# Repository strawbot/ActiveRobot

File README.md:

# Manifesto
In nature everything is connected. Inside, outside and inside to outside separated by membranes, or highly differentiated regions separating realms. The partitioning of realms and connecting of realms is life. Biomimetic forms seek to have this strategy as a backbone or more broadly, a shell. Within this shell is connectedness. A reticulated ecosystem. Through physical and time connections by remembered pasts and events. Life is lived, learned and lauded. Sometimes forgotten to relive anew. There must be sensing, filtering, analyzing, remembering, planning, pruning, and learning.

# Mission Statement
The decision to change the level of actuation in a single muscle is connected to a funnel of remembrance and motivation. A muscle also feels its actuation, usage, condition, pain and preservation. A muscle can be measured, filtered and categorized into reactions and remembered to effect a trend of behaviour. Sense of balance, change in balance, flight plan for balance all form the actuations of muscle seeking to achieve balance motivation.

# Notes
- Each board port of the platform has its own project, differences and abilities
- As abilities are developed, they can be shared and moved to the Robot folder
- Network connectivity is possible via Ethernet, USB, and PPP over serial
- Shared network applications include NTP, Telnet, HTTP
- The HTTP web server provides a way to communicate with the board through a command line and observe robotic elements via a line graph and 3D visual element

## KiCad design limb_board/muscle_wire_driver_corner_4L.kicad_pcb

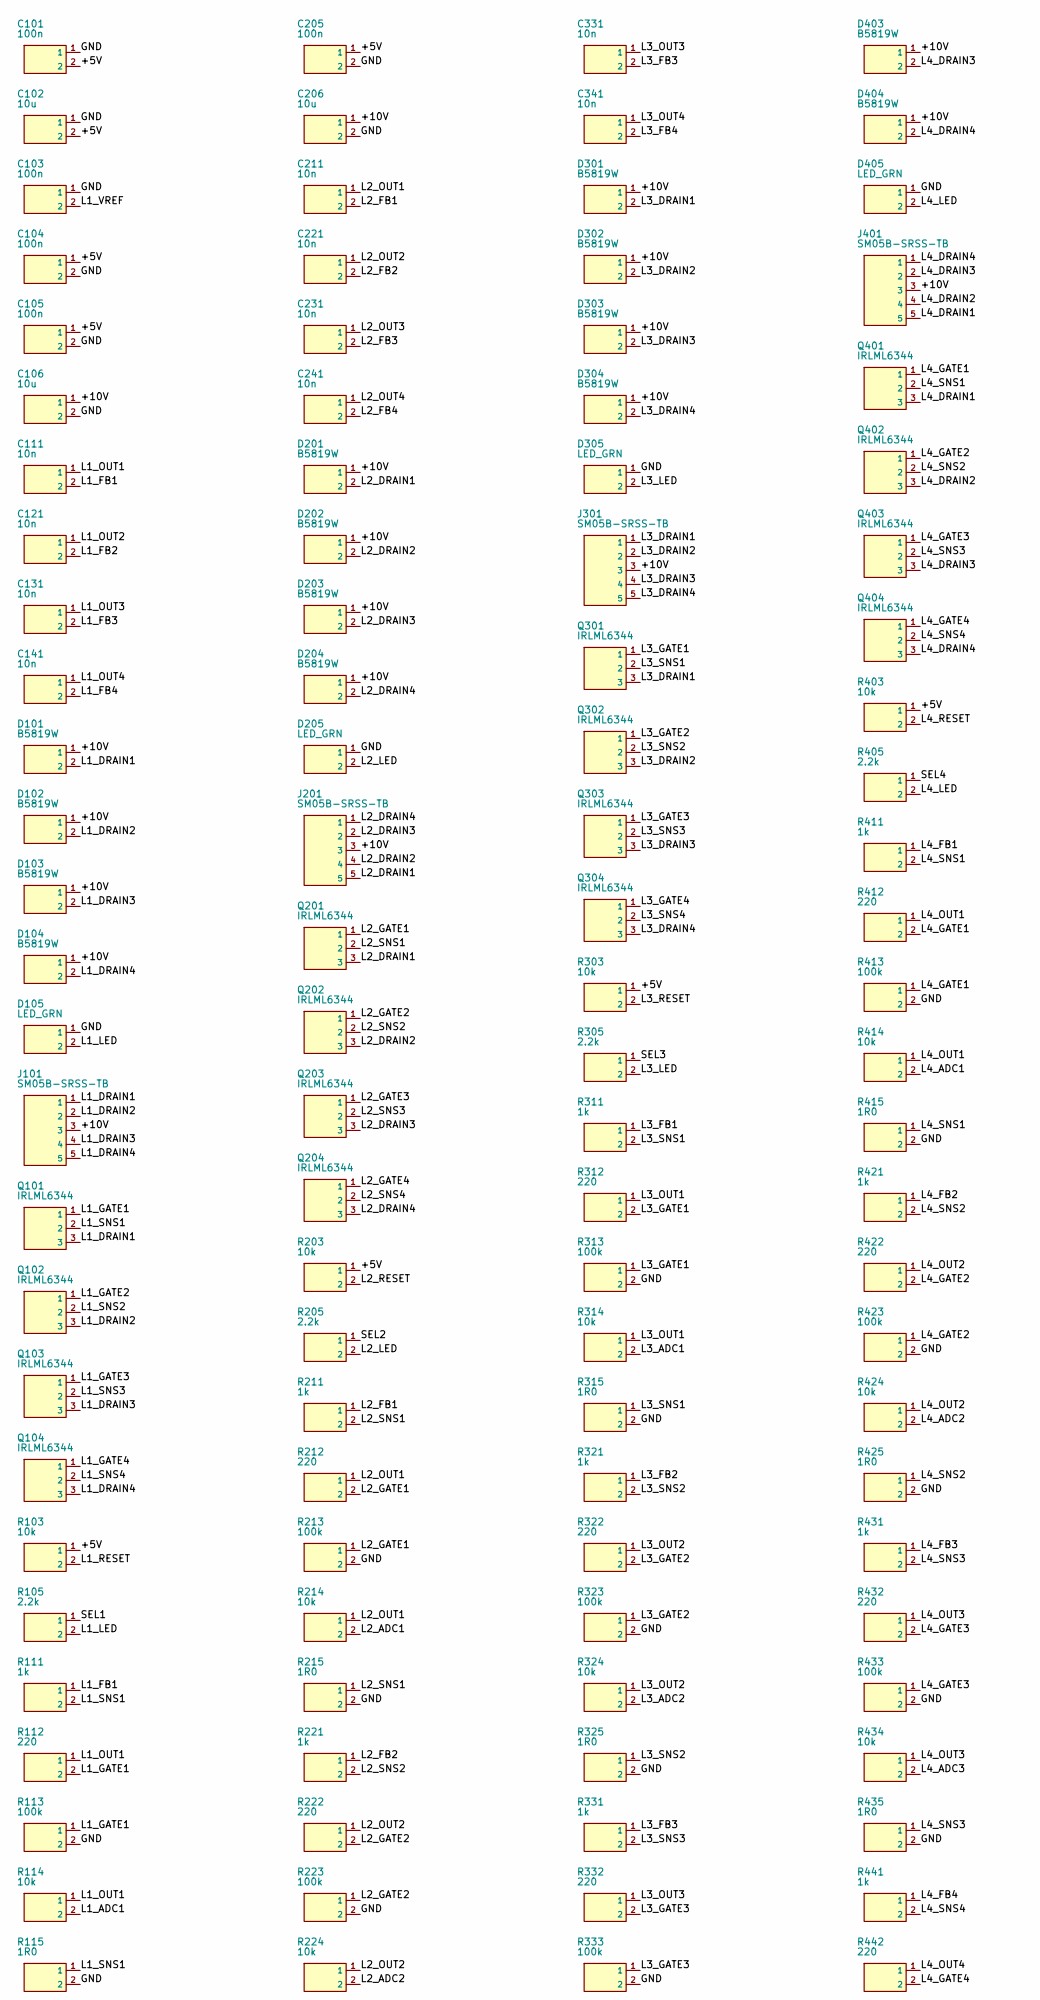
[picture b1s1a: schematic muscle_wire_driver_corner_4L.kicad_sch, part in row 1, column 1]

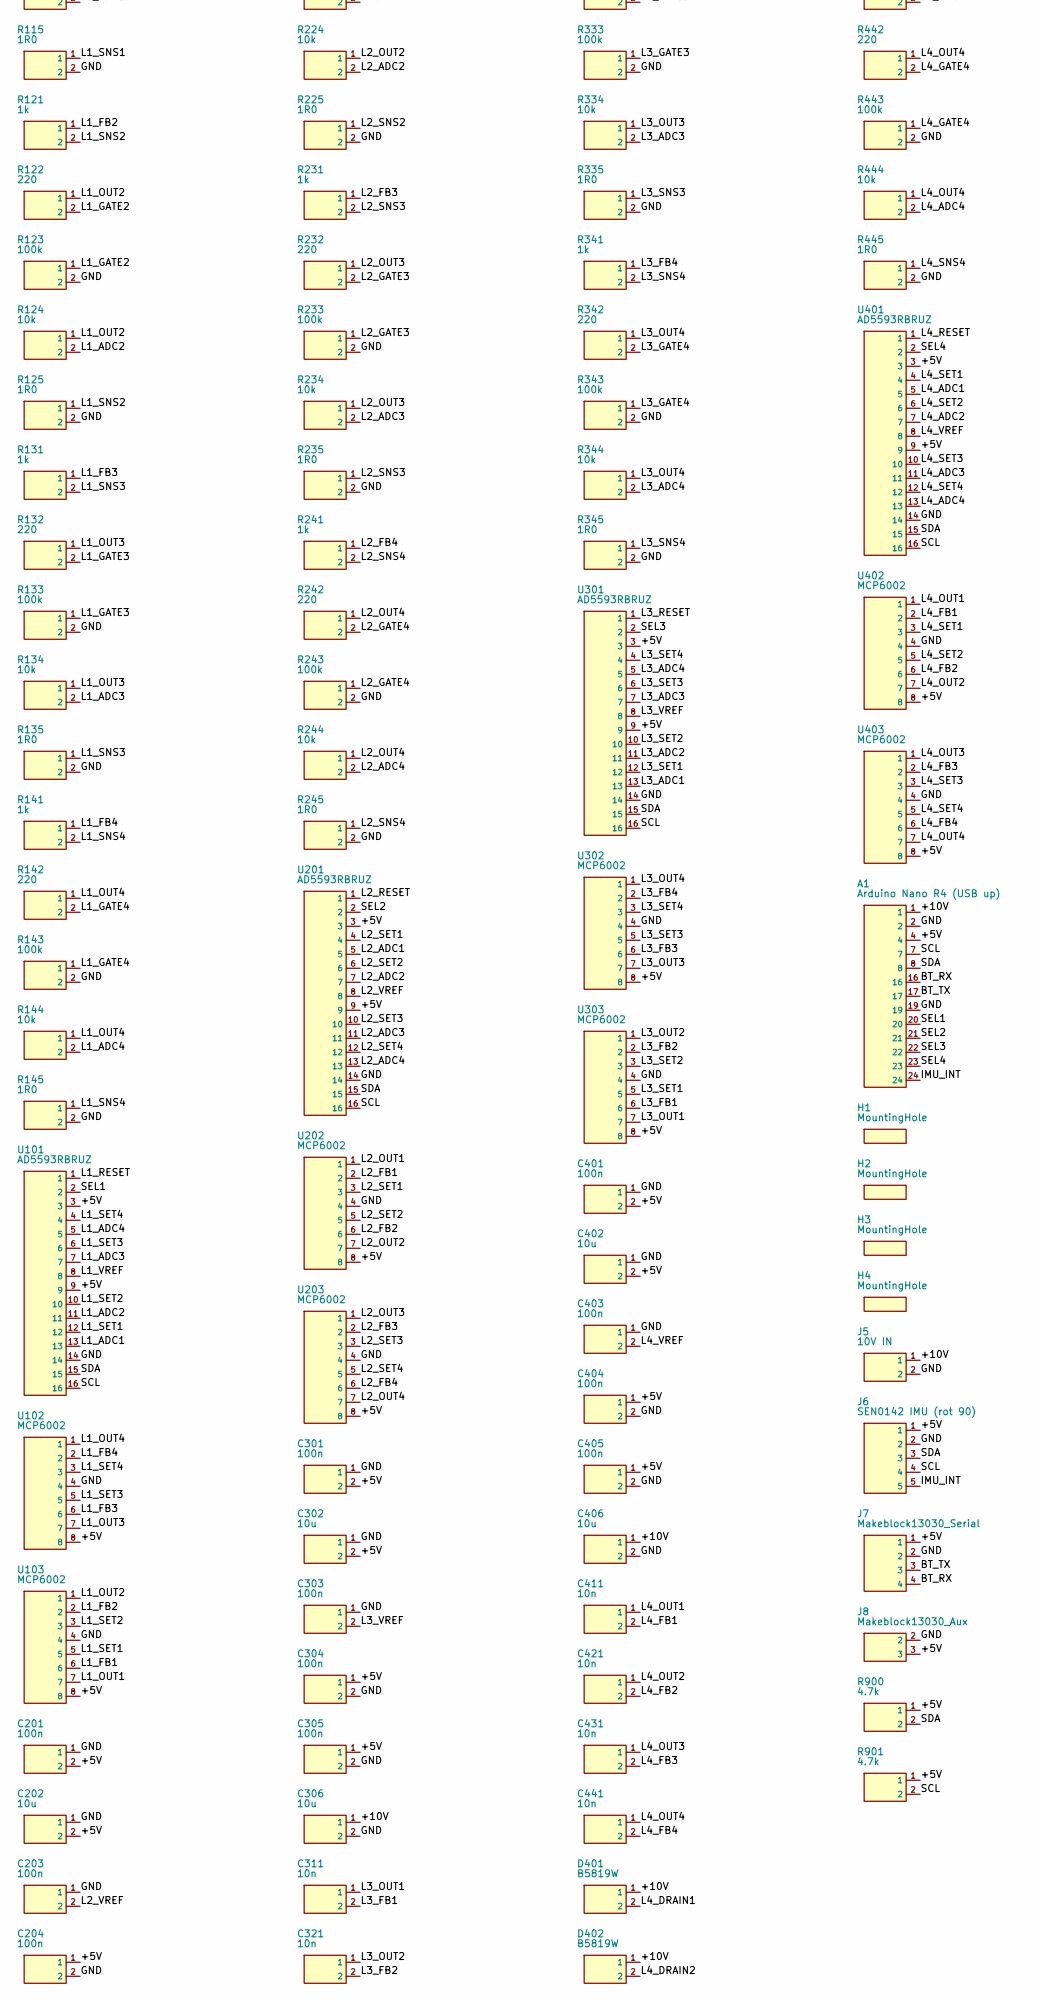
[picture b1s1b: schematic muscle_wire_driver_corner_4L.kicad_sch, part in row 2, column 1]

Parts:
A1: Arduino Nano R4 (USB up); ArduinoNanoR4_Socket
C101, C103, C104, C105, C201, C203, C204, C205, C301, C303, C304, C305, C401, C403, C404, C405: 100n; C_0603_1608Metric
C102, C106, C202, C206, C302, C306, C402, C406: 10u; C_0805_2012Metric
C111, C121, C131, C141, C211, C221, C231, C241, C311, C321, C331, C341, C411, C421, C431, C441: 10n; C_0603_1608Metric
D101, D102, D103, D104, D201, D202, D203, D204, D301, D302, D303, D304, D401, D402, D403, D404: B5819W; D_SOD-123
D105, D205, D305, D405: LED_GRN; LED_0603_1608Metric
H1, H2, H3, H4: MountingHole; MountingHole_2.7mm
J5: 10V IN; TerminalBlock_2P_5.08
J6: SEN0142 IMU (rot 90); SEN0142_IMU_1x05
J7: Makeblock13030_Serial
J8: Makeblock13030_Aux
J101, J201, J301, J401: SM05B-SRSS-TB; JST_SH_SM05B-SRSS-TB_1x05-1MP_P1.00mm_Horizontal
Q101, Q102, Q103, Q104, Q201, Q202, Q203, Q204, Q301, Q302, Q303, Q304, Q401, Q402, Q403, Q404: IRLML6344; SOT-23
R103, R114, R124, R134, R144, R203, R214, R224, R234, R244, R303, R314, R324, R334, R344, R403, R414, R424, R434, R444: 10k; R_0603_1608Metric
R105, R205, R305, R405: 2.2k; R_0603_1608Metric
R111, R121, R131, R141, R211, R221, R231, R241, R311, R321, R331, R341, R411, R421, R431, R441: 1k; R_0603_1608Metric
R112, R122, R132, R142, R212, R222, R232, R242, R312, R322, R332, R342, R412, R422, R432, R442: 220; R_0603_1608Metric
R113, R123, R133, R143, R213, R223, R233, R243, R313, R323, R333, R343, R413, R423, R433, R443: 100k; R_0603_1608Metric
R115, R125, R135, R145, R215, R225, R235, R245, R315, R325, R335, R345, R415, R425, R435, R445: 1R0; R_1206_3216Metric
R900, R901: 4.7k; R_0603_1608Metric
U101, U201, U301, U401: AD5593RBRUZ; TSSOP-16_4.4x5mm_P0.65mm
U102, U103, U202, U203, U302, U303, U402, U403: MCP6002; SOIC-8_3.9x4.9mm_P1.27mm

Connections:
+5V: A1.4, C101.2, C102.2, C104.1, C105.1, C201.2, C202.2, C204.1, C205.1, C301.2, C302.2, C304.1, C305.1, C401.2, C402.2, C404.1, C405.1, J6.1, J7.1, J8.3, R103.1, R203.1, R303.1, R403.1, R900.1, R901.1, U101.3, U101.9, U102.8, U103.8, U201.3, U201.9, U202.8, U203.8, U301.3, U301.9, U302.8, U303.8, U401.3, U401.9, U402.8, U403.8
+10V: A1.1, C106.1, C206.1, C306.1, C406.1, D101.1, D102.1, D103.1, D104.1, D201.1, D202.1, D203.1, D204.1, D301.1, D302.1, D303.1, D304.1, D401.1, D402.1, D403.1, D404.1, J5.1, J101.3, J201.3, J301.3, J401.3
BT_RX: A1.16, J7.4
BT_TX: A1.17, J7.3
GND: A1.2, A1.19, C101.1, C102.1, C103.1, C104.2, C105.2, C106.2, C201.1, C202.1, C203.1, C204.2, C205.2, C206.2, C301.1, C302.1, C303.1, C304.2, C305.2, C306.2, C401.1, C402.1, C403.1, C404.2, C405.2, C406.2, D105.1, D205.1, D305.1, D405.1, J5.2, J6.2, J7.2, J8.2, R113.2, R115.2, R123.2, R125.2, R133.2, R135.2, R143.2, R145.2, R213.2, R215.2, R223.2, R225.2, R233.2, R235.2, R243.2, R245.2, R313.2, R315.2, R323.2, R325.2, R333.2, R335.2, R343.2, R345.2, R413.2, R415.2, R423.2, R425.2, R433.2, R435.2, R443.2, R445.2, U101.14, U102.4, U103.4, U201.14, U202.4, U203.4, U301.14, U302.4, U303.4, U401.14, U402.4, U403.4
IMU_INT: A1.24, J6.5
L1_ADC1: R114.2, U101.13
L1_ADC2: R124.2, U101.11
L1_ADC3: R134.2, U101.7
L1_ADC4: R144.2, U101.5
L1_DRAIN1: D101.2, J101.1, Q101.3
L1_DRAIN2: D102.2, J101.2, Q102.3
L1_DRAIN3: D103.2, J101.4, Q103.3
L1_DRAIN4: D104.2, J101.5, Q104.3
L1_FB1: C111.2, R111.1, U103.6
L1_FB2: C121.2, R121.1, U103.2
L1_FB3: C131.2, R131.1, U102.6
L1_FB4: C141.2, R141.1, U102.2
L1_GATE1: Q101.1, R112.2, R113.1
L1_GATE2: Q102.1, R122.2, R123.1
L1_GATE3: Q103.1, R132.2, R133.1
L1_GATE4: Q104.1, R142.2, R143.1
L1_LED: D105.2, R105.2
L1_OUT1: C111.1, R112.1, R114.1, U103.7
L1_OUT2: C121.1, R122.1, R124.1, U103.1
L1_OUT3: C131.1, R132.1, R134.1, U102.7
L1_OUT4: C141.1, R142.1, R144.1, U102.1
L1_RESET: R103.2, U101.1
L1_SET1: U101.12, U103.5
L1_SET2: U101.10, U103.3
L1_SET3: U101.6, U102.5
L1_SET4: U101.4, U102.3
L1_SNS1: Q101.2, R111.2, R115.1
L1_SNS2: Q102.2, R121.2, R125.1
L1_SNS3: Q103.2, R131.2, R135.1
L1_SNS4: Q104.2, R141.2, R145.1
L1_VREF: C103.2, U101.8
L2_ADC1: R214.2, U201.5
L2_ADC2: R224.2, U201.7
L2_ADC3: R234.2, U201.11
L2_ADC4: R244.2, U201.13
L2_DRAIN1: D201.2, J201.5, Q201.3
L2_DRAIN2: D202.2, J201.4, Q202.3
L2_DRAIN3: D203.2, J201.2, Q203.3
L2_DRAIN4: D204.2, J201.1, Q204.3
L2_FB1: C211.2, R211.1, U202.2
L2_FB2: C221.2, R221.1, U202.6
L2_FB3: C231.2, R231.1, U203.2
L2_FB4: C241.2, R241.1, U203.6
L2_GATE1: Q201.1, R212.2, R213.1
L2_GATE2: Q202.1, R222.2, R223.1
L2_GATE3: Q203.1, R232.2, R233.1
L2_GATE4: Q204.1, R242.2, R243.1
L2_LED: D205.2, R205.2
L2_OUT1: C211.1, R212.1, R214.1, U202.1
L2_OUT2: C221.1, R222.1, R224.1, U202.7
L2_OUT3: C231.1, R232.1, R234.1, U203.1
L2_OUT4: C241.1, R242.1, R244.1, U203.7
L2_RESET: R203.2, U201.1
L2_SET1: U201.4, U202.3
L2_SET2: U201.6, U202.5
L2_SET3: U201.10, U203.3
L2_SET4: U201.12, U203.5
L2_SNS1: Q201.2, R211.2, R215.1
L2_SNS2: Q202.2, R221.2, R225.1
L2_SNS3: Q203.2, R231.2, R235.1
L2_SNS4: Q204.2, R241.2, R245.1
L2_VREF: C203.2, U201.8
L3_ADC1: R314.2, U301.13
L3_ADC2: R324.2, U301.11
L3_ADC3: R334.2, U301.7
L3_ADC4: R344.2, U301.5
L3_DRAIN1: D301.2, J301.1, Q301.3
L3_DRAIN2: D302.2, J301.2, Q302.3
L3_DRAIN3: D303.2, J301.4, Q303.3
L3_DRAIN4: D304.2, J301.5, Q304.3
L3_FB1: C311.2, R311.1, U303.6
L3_FB2: C321.2, R321.1, U303.2
L3_FB3: C331.2, R331.1, U302.6
L3_FB4: C341.2, R341.1, U302.2
L3_GATE1: Q301.1, R312.2, R313.1
L3_GATE2: Q302.1, R322.2, R323.1
L3_GATE3: Q303.1, R332.2, R333.1
L3_GATE4: Q304.1, R342.2, R343.1
L3_LED: D305.2, R305.2
L3_OUT1: C311.1, R312.1, R314.1, U303.7
L3_OUT2: C321.1, R322.1, R324.1, U303.1
L3_OUT3: C331.1, R332.1, R334.1, U302.7
L3_OUT4: C341.1, R342.1, R344.1, U302.1
L3_RESET: R303.2, U301.1
L3_SET1: U301.12, U303.5
L3_SET2: U301.10, U303.3
L3_SET3: U301.6, U302.5
L3_SET4: U301.4, U302.3
L3_SNS1: Q301.2, R311.2, R315.1
L3_SNS2: Q302.2, R321.2, R325.1
L3_SNS3: Q303.2, R331.2, R335.1
L3_SNS4: Q304.2, R341.2, R345.1
L3_VREF: C303.2, U301.8
L4_ADC1: R414.2, U401.5
L4_ADC2: R424.2, U401.7
L4_ADC3: R434.2, U401.11
L4_ADC4: R444.2, U401.13
L4_DRAIN1: D401.2, J401.5, Q401.3
L4_DRAIN2: D402.2, J401.4, Q402.3
L4_DRAIN3: D403.2, J401.2, Q403.3
L4_DRAIN4: D404.2, J401.1, Q404.3
L4_FB1: C411.2, R411.1, U402.2
L4_FB2: C421.2, R421.1, U402.6
L4_FB3: C431.2, R431.1, U403.2
L4_FB4: C441.2, R441.1, U403.6
L4_GATE1: Q401.1, R412.2, R413.1
L4_GATE2: Q402.1, R422.2, R423.1
L4_GATE3: Q403.1, R432.2, R433.1
L4_GATE4: Q404.1, R442.2, R443.1
L4_LED: D405.2, R405.2
L4_OUT1: C411.1, R412.1, R414.1, U402.1
L4_OUT2: C421.1, R422.1, R424.1, U402.7
L4_OUT3: C431.1, R432.1, R434.1, U403.1
L4_OUT4: C441.1, R442.1, R444.1, U403.7
L4_RESET: R403.2, U401.1
L4_SET1: U401.4, U402.3
L4_SET2: U401.6, U402.5
L4_SET3: U401.10, U403.3
L4_SET4: U401.12, U403.5
L4_SNS1: Q401.2, R411.2, R415.1
L4_SNS2: Q402.2, R421.2, R425.1
L4_SNS3: Q403.2, R431.2, R435.1
L4_SNS4: Q404.2, R441.2, R445.1
L4_VREF: C403.2, U401.8
SCL: A1.7, J6.4, R901.2, U101.16, U201.16, U301.16, U401.16
SDA: A1.8, J6.3, R900.2, U101.15, U201.15, U301.15, U401.15
SEL1: A1.20, R105.1, U101.2
SEL2: A1.21, R205.1, U201.2
SEL3: A1.22, R305.1, U301.2
SEL4: A1.23, R405.1, U401.2

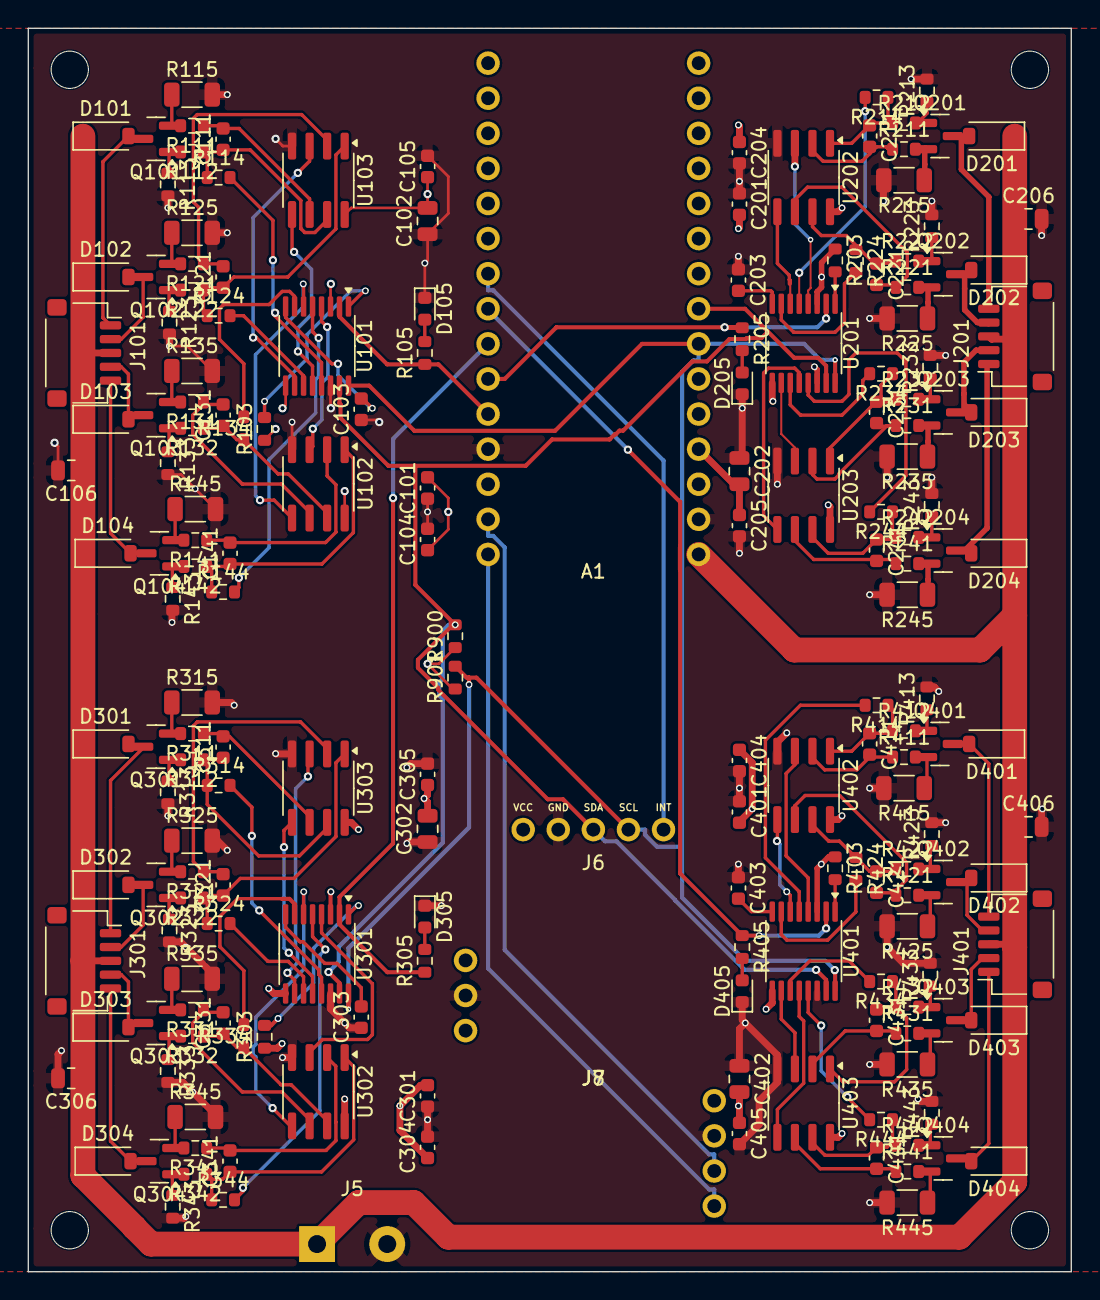
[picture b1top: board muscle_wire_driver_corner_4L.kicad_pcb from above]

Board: 4 copper layers, 75.5 x 90.0 mm, 191 parts (0 on the bottom side), 136 nets.

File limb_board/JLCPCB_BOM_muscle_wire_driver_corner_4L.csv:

Comment,Designator,Footprint,LCSC Part #
100n,"C101,C103,C104,C105,C201,C203,C204,C205,C301,C303,C304,C305,C401,C403,C404,C405",C_0603_1608Metric,
10u,"C102,C106,C202,C206,C302,C306,C402,C406",C_0805_2012Metric,
10n,"C111,C121,C131,C141,C211,C221,C231,C241,C311,C321,C331,C341,C411,C421,C431,C441",C_0603_1608Metric,
B5819W,"D101,D102,D103,D104,D201,D202,D203,D204,D301,D302,D303,D304,D401,D402,D403,D404",D_SOD-123,C8598
LED_GRN,"D105,D205,D305,D405",LED_0603_1608Metric,C72043
SM05B-SRSS-TB,"J101,J201,J301,J401",JST_SH_SM05B-SRSS-TB_1x05-1MP_P1.00mm_Horizontal,C136657
IRLML6344,"Q101,Q102,Q103,Q104,Q201,Q202,Q203,Q204,Q301,Q302,Q303,Q304,Q401,Q402,Q403,Q404",SOT-23,C53550
10k,"R103,R114,R124,R134,R144,R203,R214,R224,R234,R244,R303,R314,R324,R334,R344,R403,R414,R424,R434,R444",R_0603_1608Metric,
2.2k,"R105,R205,R305,R405",R_0603_1608Metric,
1k,"R111,R121,R131,R141,R211,R221,R231,R241,R311,R321,R331,R341,R411,R421,R431,R441",R_0603_1608Metric,
220,"R112,R122,R132,R142,R212,R222,R232,R242,R312,R322,R332,R342,R412,R422,R432,R442",R_0603_1608Metric,
100k,"R113,R123,R133,R143,R213,R223,R233,R243,R313,R323,R333,R343,R413,R423,R433,R443",R_0603_1608Metric,
1R0,"R115,R125,R135,R145,R215,R225,R235,R245,R315,R325,R335,R345,R415,R425,R435,R445",R_1206_3216Metric,
4.7k,"R900,R901",R_0603_1608Metric,
AD5593RBRUZ,"U101,U201,U301,U401",TSSOP-16_4.4x5mm_P0.65mm,C207507
MCP6002,"U102,U103,U202,U203,U302,U303,U402,U403",SOIC-8_3.9x4.9mm_P1.27mm,C116706

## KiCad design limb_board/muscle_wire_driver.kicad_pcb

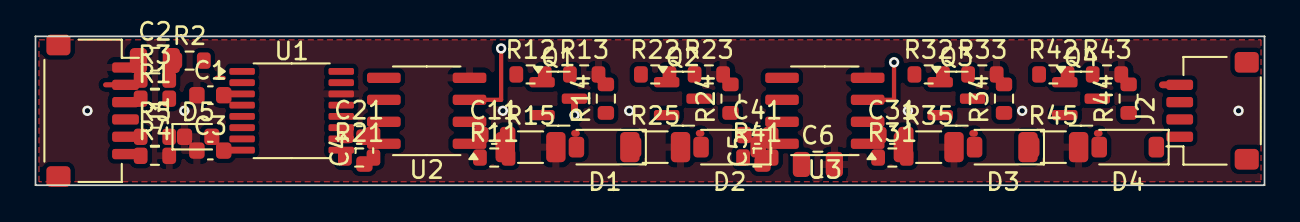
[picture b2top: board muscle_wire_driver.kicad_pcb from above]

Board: 2 copper layers, 71.0 x 8.6 mm, 49 parts (0 on the bottom side), 37 nets.

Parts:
C1, C3, C4, C5: 100n; C_0603_1608Metric
C2, C6: 10u; C_0805_2012Metric
C11, C21, C31, C41: 10n; C_0603_1608Metric
D1, D2, D3, D4: B5819W; D_SOD-123
D5: LED_GRN; LED_0603_1608Metric
J1: SM06B-SRSS-TB; JST_SH_SM06B-SRSS-TB_1x06-1MP_P1.00mm_Horizontal
J2: SM04B-SRSS-TB; JST_SH_SM04B-SRSS-TB_1x04-1MP_P1.00mm_Horizontal
Q1, Q2, Q3, Q4: IRLML6344; SOT-23
R1, R2: 4.7k; R_0603_1608Metric
R3, R4, R14, R24, R34, R44: 10k; R_0603_1608Metric
R5: 2.2k; R_0603_1608Metric
R11, R21, R31, R41: 1k; R_0603_1608Metric
R12, R22, R32, R42: 220; R_0603_1608Metric
R13, R23, R33, R43: 100k; R_0603_1608Metric
R15, R25, R35, R45: 1R0; R_1206_3216Metric
U1: AD5593RBRUZ; TSSOP-16_4.4x5mm_P0.65mm
U2, U3: MCP6002; SOIC-8_3.9x4.9mm_P1.27mm

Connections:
+10V: C6.1, D1.1, D2.1, D3.1, D4.1, J1.3
A0: J1.6, R4.1, R5.1, U1.2
ADC1: R14.2, U1.10
ADC2: R24.2, U1.11
ADC3: R34.2, U1.12
ADC4: R44.2, U1.13
DRAIN1: D1.2, J2.1, Q1.3
DRAIN2: D2.2, J2.2, Q2.3
DRAIN3: D3.2, J2.3, Q3.3
DRAIN4: D4.2, J2.4, Q4.3
FB1: C11.2, R11.1, U2.2
FB2: C21.2, R21.1, U2.6
FB3: C31.2, R31.1, U3.2
FB4: C41.2, R41.1, U3.6
GATE1: Q1.1, R12.2, R13.1
GATE2: Q2.1, R22.2, R23.1
GATE3: Q3.1, R32.2, R33.1
GATE4: Q4.1, R42.2, R43.1
GND: C1.1, C2.1, C3.1, C4.2, C5.2, C6.2, D5.1, J1.1, R4.2, R13.2, R15.2, R23.2, R25.2, R33.2, R35.2, R43.2, R45.2, U1.14, U2.4, U3.4
LED_A: D5.2, R5.2
OUT1: C11.1, R12.1, R14.1, U2.1
OUT2: C21.1, R22.1, R24.1, U2.7
OUT3: C31.1, R32.1, R34.1, U3.1
OUT4: C41.1, R42.1, R44.1, U3.7
RESET_N: R3.2, U1.1
SCL: J1.5, R2.2, U1.16
SDA: J1.4, R1.2, U1.15
SET1: U1.4, U2.3
SET2: U1.5, U2.5
SET3: U1.6, U3.3
SET4: U1.7, U3.5
SNS1: Q1.2, R11.2, R15.1
SNS2: Q2.2, R21.2, R25.1
SNS3: Q3.2, R31.2, R35.1
SNS4: Q4.2, R41.2, R45.1
VCC: C1.2, C2.2, C4.1, C5.1, J1.2, R1.1, R2.1, R3.1, U1.3, U1.9, U2.8, U3.8
VREF: C3.2, U1.8

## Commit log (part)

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2026-03-21 Initial entry
2026-04-08 stop tracking in repo
2026-04-08 add to watch fors
2026-04-08 new port
2026-04-21 before the high level refactoring
2026-04-21 New board and factoring
2026-04-24 refactor canary and apply to all projects
2026-04-25 Factor code into Robot
2026-05-03 added shared http server
2026-05-03 New board port up and running
2026-05-11 more common refactoring: clocks
2026-05-11 update tiva, tos
2026-05-12 Add manifesto, mission statement, and project notes
    Added a manifesto and mission statement outlining the project's philosophy and objectives, along with notes on network connectivity and project organization.
2026-05-12 Revise headings in README for clarity
    Updated headings in README.md for better structure and readability.
2026-05-12 link in submodules
2026-05-12 link in submodules
    # Conflicts:
    # .gitmodules
    # board-Nucleo411
    # board-Nucleo446
    # board-PNucleo
2026-05-12 remove extra folders
2026-05-12 add tinyusb
2026-05-14 updated time events to work across range of board timers
